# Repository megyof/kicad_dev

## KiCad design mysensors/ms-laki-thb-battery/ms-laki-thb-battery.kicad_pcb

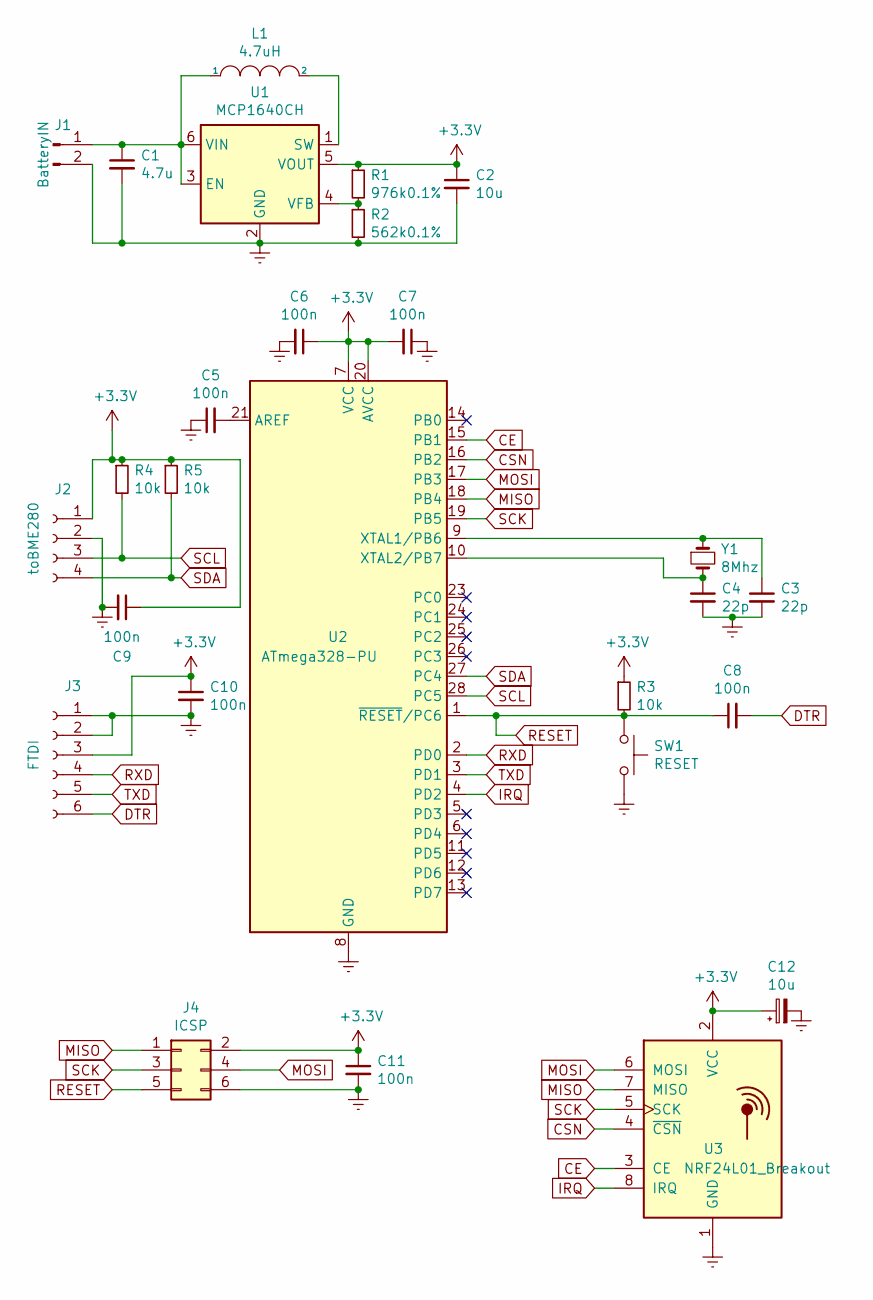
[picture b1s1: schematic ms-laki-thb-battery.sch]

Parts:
C1: 4.7u; C_1206_3216Metric_Pad1.42x1.75mm_HandSolder
C2: 10u; C_1206_3216Metric_Pad1.42x1.75mm_HandSolder
C3, C4: 22p; C_1206_3216Metric_Pad1.42x1.75mm_HandSolder
C5, C6, C7, C8, C9, C10, C11: 100n; C_1206_3216Metric_Pad1.42x1.75mm_HandSolder
C12: 10u; CP_Radial_D4.0mm_P1.50mm
J1: BatteryIN; PinHeader_1x02_P2.54mm_Vertical
J2: toBME280; PinSocket_1x04_P2.54mm_Vertical
J3: FTDI; PinSocket_1x06_P2.54mm_Vertical
J4: ICSP; PinHeader_2x03_P2.54mm_Vertical
L1: 4.7uH; L_Taiyo-Yuden_NR-60xx_HandSoldering
R1: 976k0.1%; R_Axial_DIN0207_L6.3mm_D2.5mm_P7.62mm_Horizontal
R2: 562k0.1%; R_Axial_DIN0207_L6.3mm_D2.5mm_P7.62mm_Horizontal
R3, R4, R5: 10k; R_1206_3216Metric_Pad1.42x1.75mm_HandSolder
SW1: RESET; SW_SPST_FSMSM
U1: MCP1640CH; SOT-23-6
U2: ATmega328-PU; DIP-28_W7.62mm_Socket_LongPads
U3: NRF24L01_Breakout; nRF24L01_Breakout
Y1: 8Mhz; Crystal_HC49-U_Vertical

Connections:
+3V3: C2.1, C6.1, C7.2, C9.1, C10.1, C11.1, C12.1, J2.1, J3.3, J4.2, R1.1, R3.1, R4.1, R5.1, U1.5 (VOUT), U2.7 (VCC), U2.20 (AVCC), U3.2 (VCC)
CE: U2.15 (PB1), U3.3 (CE)
CSN: U2.16 (PB2), U3.4 (~CSN)
DTR: C8.2, J3.6
Earth: C1.2, C2.2, C3.2, C4.2, C5.1, C6.2, C7.1, C9.2, C10.2, C11.2, C12.2, J1.2, J2.2, J3.1, J3.2, J4.6, R2.2, SW1.2, U1.2 (GND), U2.8 (GND), U2.22 (GND), U3.1 (GND)
IRQ: U2.4 (PD2), U3.8 (IRQ)
MISO: J4.1, U2.18 (PB4), U3.7 (MISO)
MOSI: J4.4, U2.17 (PB3), U3.6 (MOSI)
unnamed: C1.1, J1.1, L1.1, U1.3 (EN), U1.6 (VIN)
unnamed: C3.1, U2.9 (XTAL1/PB6), Y1.1
unnamed: C4.1, U2.10 (XTAL2/PB7), Y1.2
unnamed: C5.2, U2.21 (AREF)
unnamed: L1.2, U1.1 (SW)
unnamed: R1.2, R2.1, U1.4 (VFB)
RESET: C8.1, J4.5, R3.2, SW1.1, U2.1 (~RESET~/PC6)
RXD: J3.4, U2.2 (PD0)
SCK: J4.3, U2.19 (PB5), U3.5 (SCK)
SCL: J2.3, R4.2, U2.28 (PC5)
SDA: J2.4, R5.2, U2.27 (PC4)
TXD: J3.5, U2.3 (PD1)

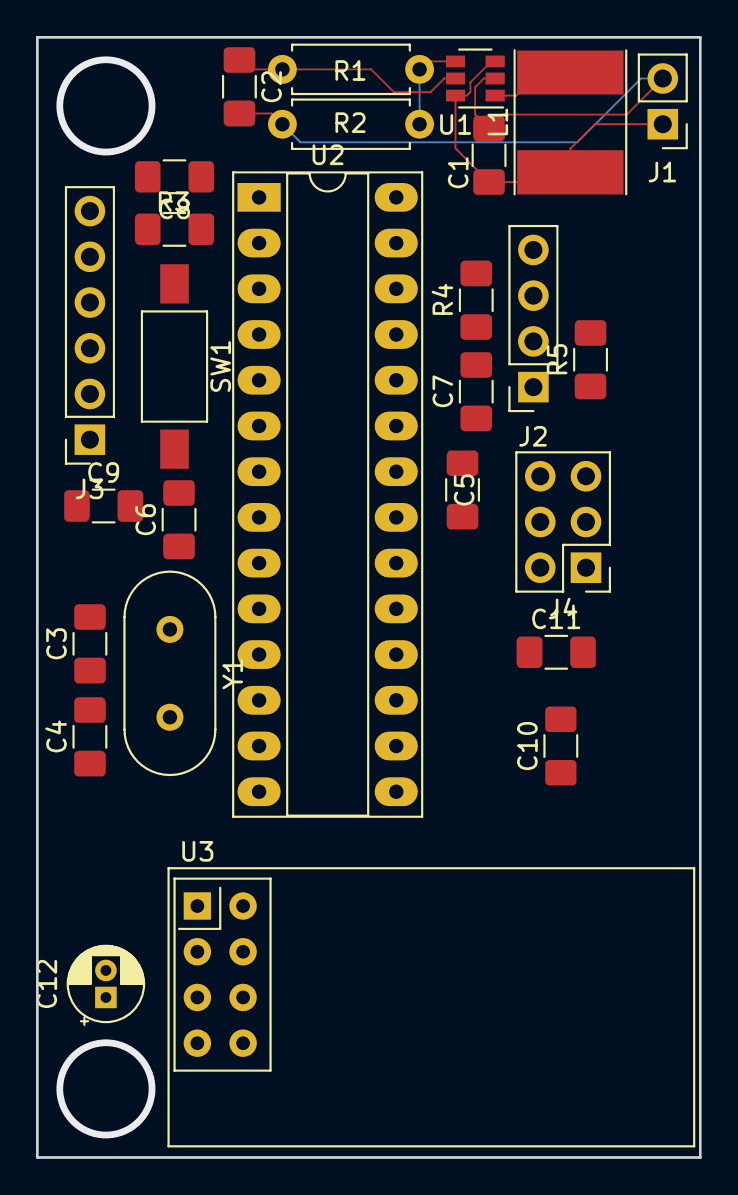
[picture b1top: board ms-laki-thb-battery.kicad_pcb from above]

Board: 2 copper layers, 36.8 x 62.2 mm, 27 parts (0 on the bottom side), 20 nets.

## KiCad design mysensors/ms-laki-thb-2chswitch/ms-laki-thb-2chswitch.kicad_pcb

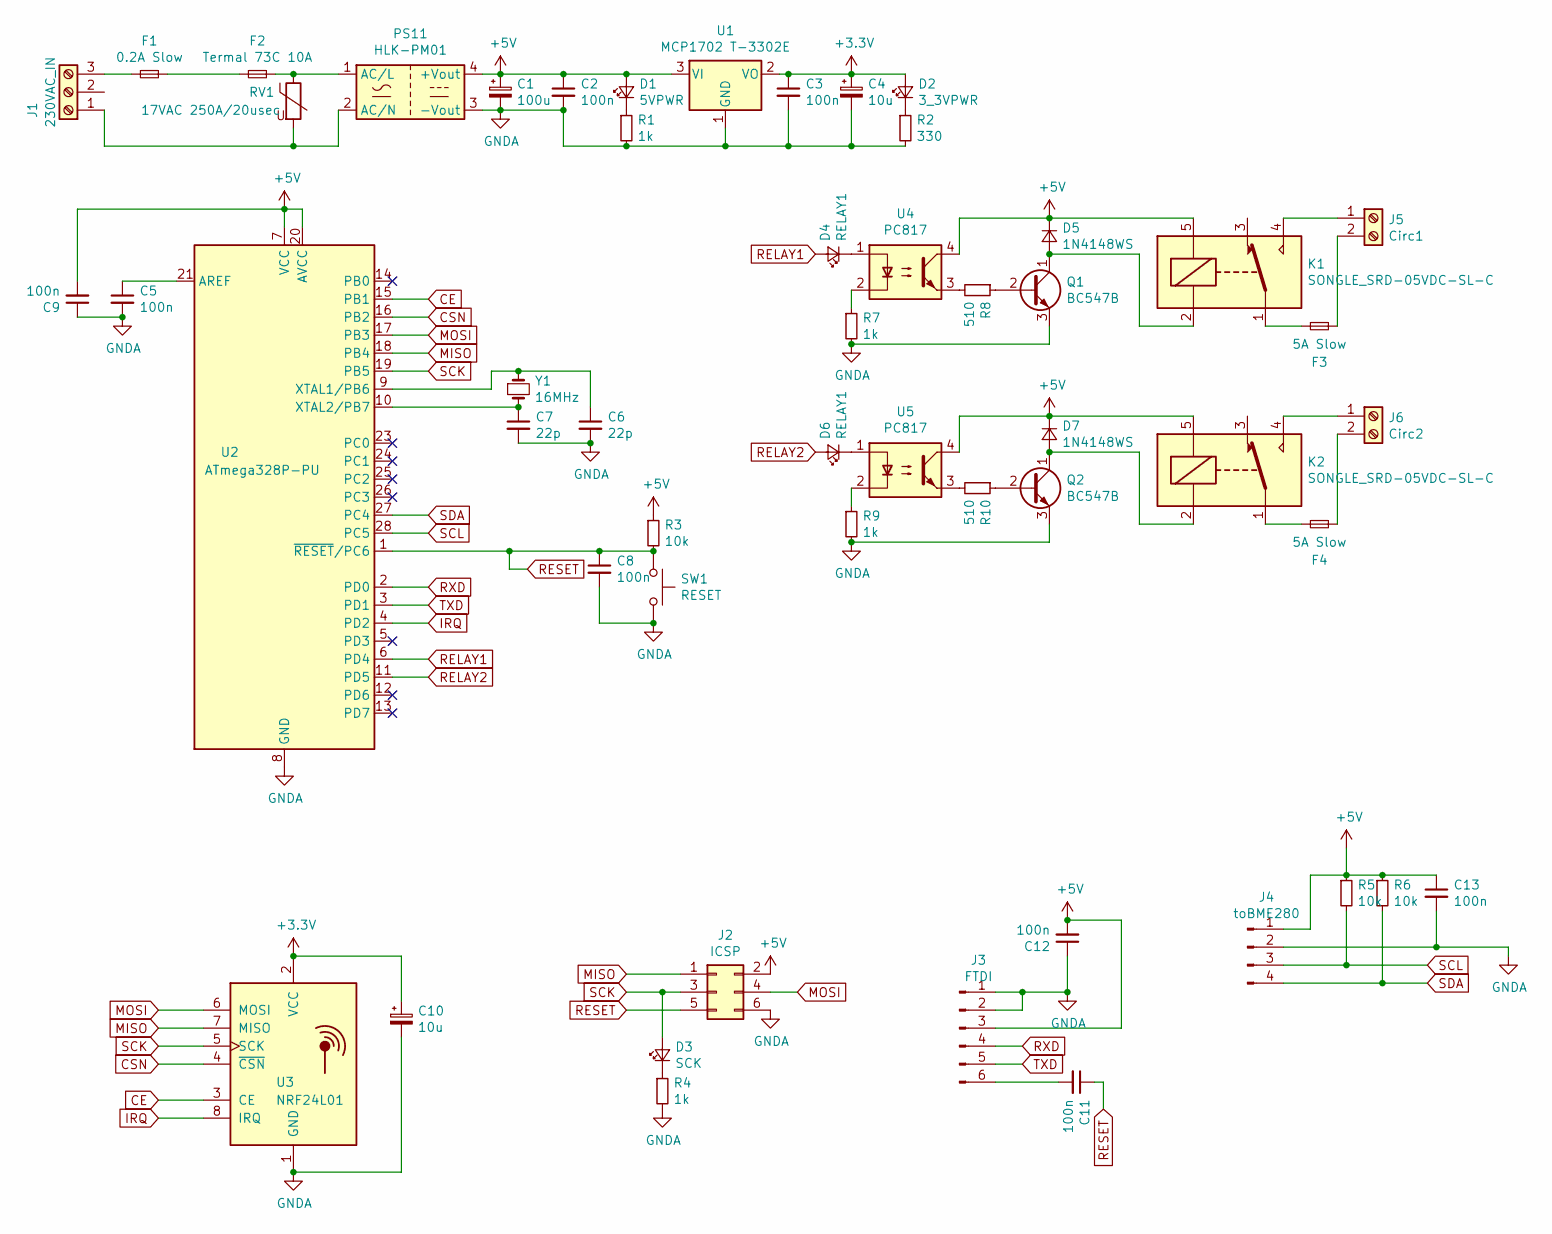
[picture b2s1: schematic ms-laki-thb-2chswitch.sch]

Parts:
C1: 100u; CP_Radial_D8.0mm_P3.50mm
C2, C3, C5, C8, C9, C11, C12, C13: 100n; C_0805_2012Metric_Pad1.15x1.40mm_HandSolder
C4, C10: 10u; CP_Radial_D4.0mm_P1.50mm
C6, C7: 22p; C_Disc_D3.0mm_W1.6mm_P2.50mm
D1: 5VPWR; D_0805_2012Metric_Pad1.15x1.40mm_HandSolder
D2: 3_3VPWR; D_0805_2012Metric_Pad1.15x1.40mm_HandSolder
D3: SCK; D_0805_2012Metric_Pad1.15x1.40mm_HandSolder
D4, D6: RELAY1; D_0805_2012Metric_Pad1.15x1.40mm_HandSolder
D5, D7: 1N4148WS; D_SOD-323_HandSoldering
F1: 0.2A Slow; Fuseholder_TR5_Littelfuse_No560_No460
F2: Termal 73C 10A; Fuse_Bourns_MF-RG300
F3, F4: 5A Slow; Fuseholder_Cylinder-5x20mm_Stelvio-Kontek_PTF78_Horizontal_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
J1: 230VAC_IN; TerminalBlock_4Ucon_1x03_P3.50mm_Vertical
J2: ICSP; PinHeader_2x03_P2.54mm_Vertical
J3: FTDI; PinSocket_1x06_P2.54mm_Vertical
J4: toBME280; PinSocket_1x04_P2.54mm_Vertical
J5: Circ1; TerminalBlock_4Ucon_1x02_P3.50mm_Vertical
J6: Circ2; TerminalBlock_4Ucon_1x02_P3.50mm_Vertical
K1, K2: SONGLE_SRD-05VDC-SL-C; Relay_SPDT_SANYOU_SRD_Series_Form_C
PS11: HLK-PM01; Converter_ACDC_HiLink_HLK-PMxx
Q1, Q2: BC547B; TO-92_HandSolder
R1, R4, R7, R9: 1k; R_0805_2012Metric_Pad1.15x1.40mm_HandSolder
R2: 330; R_0805_2012Metric_Pad1.15x1.40mm_HandSolder
R3, R5, R6: 10k; R_0805_2012Metric_Pad1.15x1.40mm_HandSolder
R8, R10: 510; R_0805_2012Metric_Pad1.15x1.40mm_HandSolder
RV1: 17VAC 250A/20usec; RV_Disc_D7mm_W3.4mm_P5mm
SW1: RESET; SW_SPST_CK_RS282G05A3
U1: MCP1702 T-3302E; SOT-23_Handsoldering
U2: ATmega328P-PU; DIP-28_W7.62mm_Socket
U3: NRF24L01; nRF24L01_Breakout
U4, U5: PC817; DIP-4_W7.62mm
Y1: 16MHz; Crystal_HC49-U_Vertical

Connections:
+3V3: C3.1, C4.1, C10.1, D2.2 (A), U1.2 (VO), U3.2 (VCC)
+5V: C1.1, C2.1, C9.2, C12.2, C13.1, D1.2 (A), D5.1 (K), D7.1 (K), J2.2, J3.3, J4.1, K1.5, K2.5, PS11.4 (+Vout), R3.1, R5.1, R6.1, U1.3 (VI), U2.7 (VCC), U2.20 (AVCC), U4.4, U5.4
CE: U2.15 (PB1), U3.3 (CE)
CSN: U2.16 (PB2), U3.4 (~CSN)
GNDA: C1.2, C2.2, C3.2, C4.2, C5.2, C6.2, C7.2, C8.2, C9.1, C10.2, C12.1, C13.2, J2.6, J3.1, J3.2, J4.2, PS11.3 (-Vout), Q1.3 (E), Q2.3 (E), R1.2, R2.2, R4.2, R7.2, R9.2, SW1.2, U1.1 (GND), U2.8 (GND), U2.22 (GND), U3.1 (GND)
IRQ: U2.4 (PD2), U3.8 (IRQ)
MISO: J2.1, U2.18 (PB4), U3.7 (MISO)
MOSI: J2.4, U2.17 (PB3), U3.6 (MOSI)
unnamed: C5.1, U2.21 (AREF)
unnamed: C6.1, U2.9 (XTAL1/PB6), Y1.1
unnamed: C7.1, U2.10 (XTAL2/PB7), Y1.2
unnamed: C11.2, J3.6
unnamed: D1.1 (K), R1.1
unnamed: D2.1 (K), R2.1
unnamed: D3.1 (K), R4.1
unnamed: D4.1 (K), U4.1
unnamed: D5.2 (A), K1.2, Q1.1 (C)
unnamed: D6.1 (K), U5.1
unnamed: D7.2 (A), K2.2, Q2.1 (C)
unnamed: F1.1, J1.3
unnamed: F1.2, F2.1
unnamed: F2.2, PS11.1 (AC/L), RV1.1
unnamed: F3.1, K1.1
unnamed: F3.2, J5.2
unnamed: F4.1, K2.1
unnamed: F4.2, J6.2
unnamed: J1.1, PS11.2 (AC/N), RV1.2
unnamed: J5.1, K1.4
unnamed: J6.1, K2.4
unnamed: Q1.2 (B), R8.1
unnamed: Q2.2 (B), R10.1
unnamed: R7.1, U4.2
unnamed: R8.2, U4.3
unnamed: R9.1, U5.2
unnamed: R10.2, U5.3
RELAY1: D4.2 (A), U2.6 (PD4)
RELAY2: D6.2 (A), U2.11 (PD5)
RESET: C8.1, C11.1, J2.5, R3.2, SW1.1, U2.1 (~RESET~/PC6)
RXD: J3.4, U2.2 (PD0)
SCK: D3.2 (A), J2.3, U2.19 (PB5), U3.5 (SCK)
SCL: J4.3, R5.2, U2.28 (PC5)
SDA: J4.4, R6.2, U2.27 (PC4)
TXD: J3.5, U2.3 (PD1)

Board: 2 copper layers, 53 parts (0 on the bottom side), 43 nets, no tracks yet.

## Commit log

2018-12-28 Initialization
2018-12-29 microcontroller is added
    Please enter the commit message for your changes. Lines starting
2018-12-29 Continue to work on it
2018-12-29 quick changes
2018-12-29 working on psu piece
2018-12-29 analog piece
2019-01-04 directory structure fix
2019-01-04 battery schemtics finsihed
